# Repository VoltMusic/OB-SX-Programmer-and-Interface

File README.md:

# OB-SX-Programmer-and-Interface
This contains the Arduino code and KiCAD project file for creating a OB-SX Programmer and Interface.

The Interface plugs into the D-sub connector at the back of the OB-SX. It accesses the OB-XA's RAM and overwrites data linked to the voice board parameters.
The Programmer allows the user to program each parameter of the voices by sending messages to the Interface over a IC2 bus.

The RAM layout file shows how the parameters, key and gate signals are stored in RAM memory (can't promise this is %100 correct). Thank you to Prehistoricman for helping reverse-engineer the ROM of the OB-SX to find these relevant address locations.

I may re-visit this project again but design the board around the more powerfull teensy microcontroller. I had many issues with the slowness and memory leakage of the arduino.

Problems:
- And extra diode is required on the programmer board, I will update the PCB with this correction soon
- As you can see in the interface code the MIDI part is commented out, this is because it has many issues currently.

To-do:
- Upload example SD card patch files

Disclaimer:
- By using the code and PCB design files included in this repository, you take responsibility of any damage that may occur to your OB-SX. I highly recommend using these materials as a starting point for you to add and improve upon, if you do not have a good understanding of electronics and (Arduino) programming I do not recommend this project. These designs are open-source and therefore can be used as you wish.

Thank you

- Nile (Volter, VoltMusic)

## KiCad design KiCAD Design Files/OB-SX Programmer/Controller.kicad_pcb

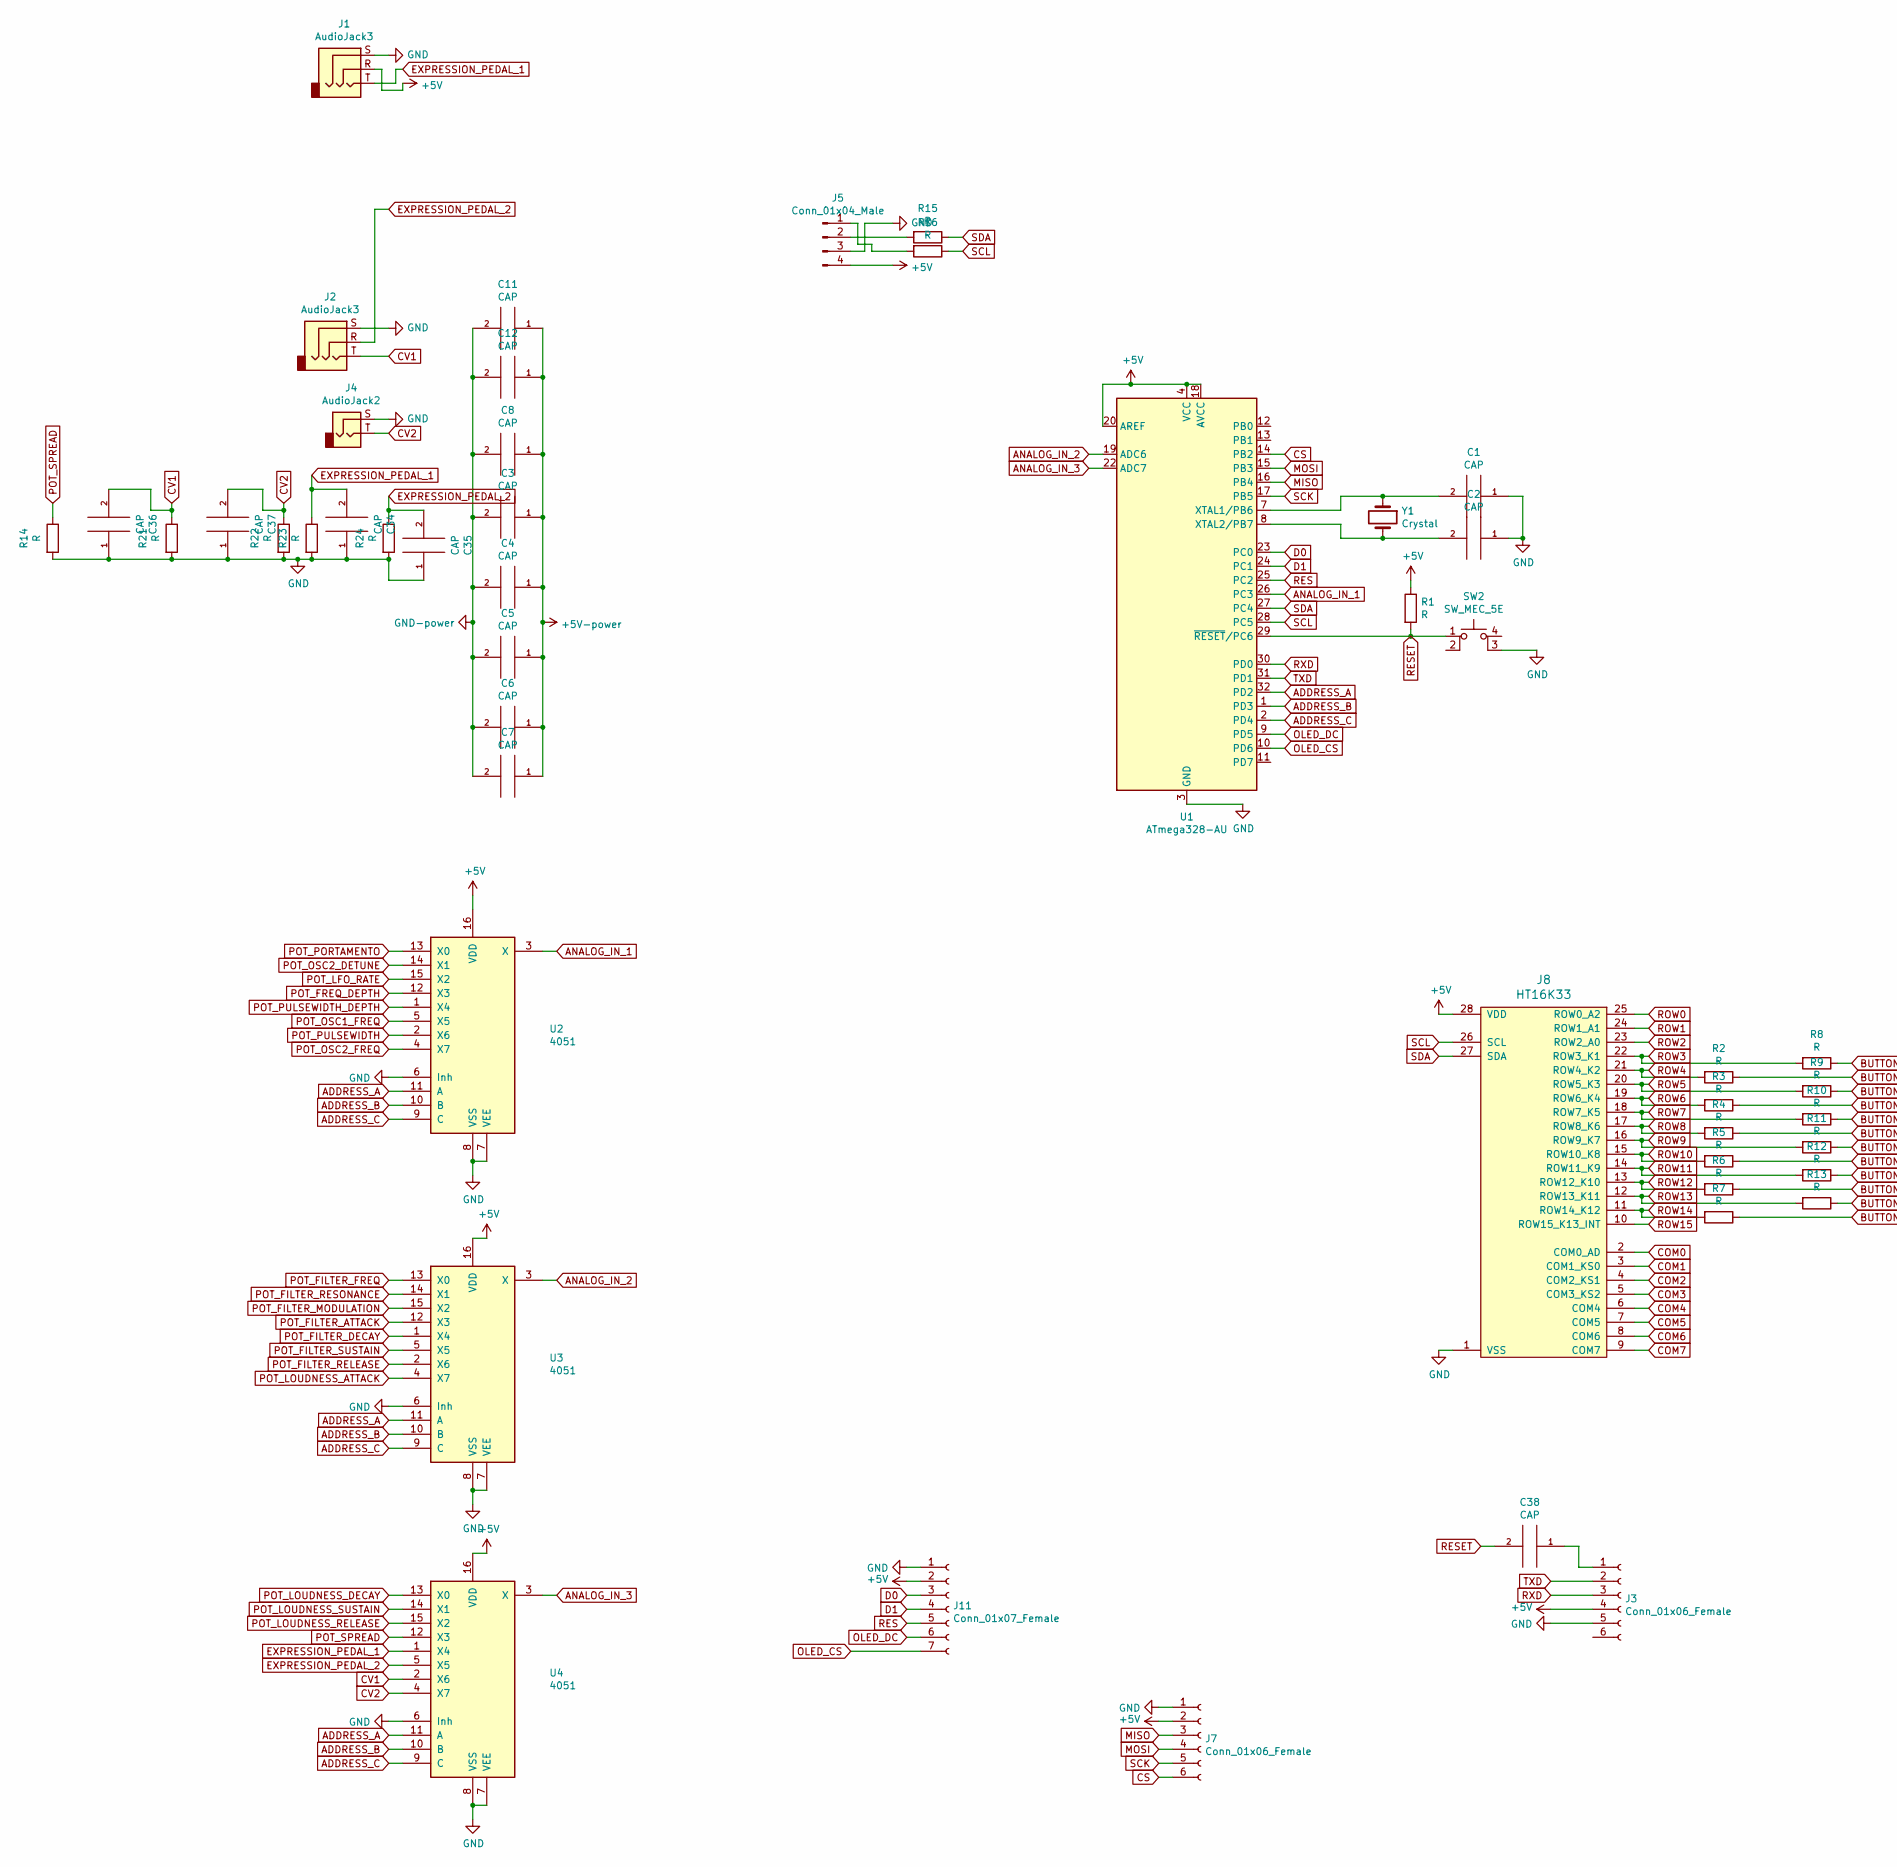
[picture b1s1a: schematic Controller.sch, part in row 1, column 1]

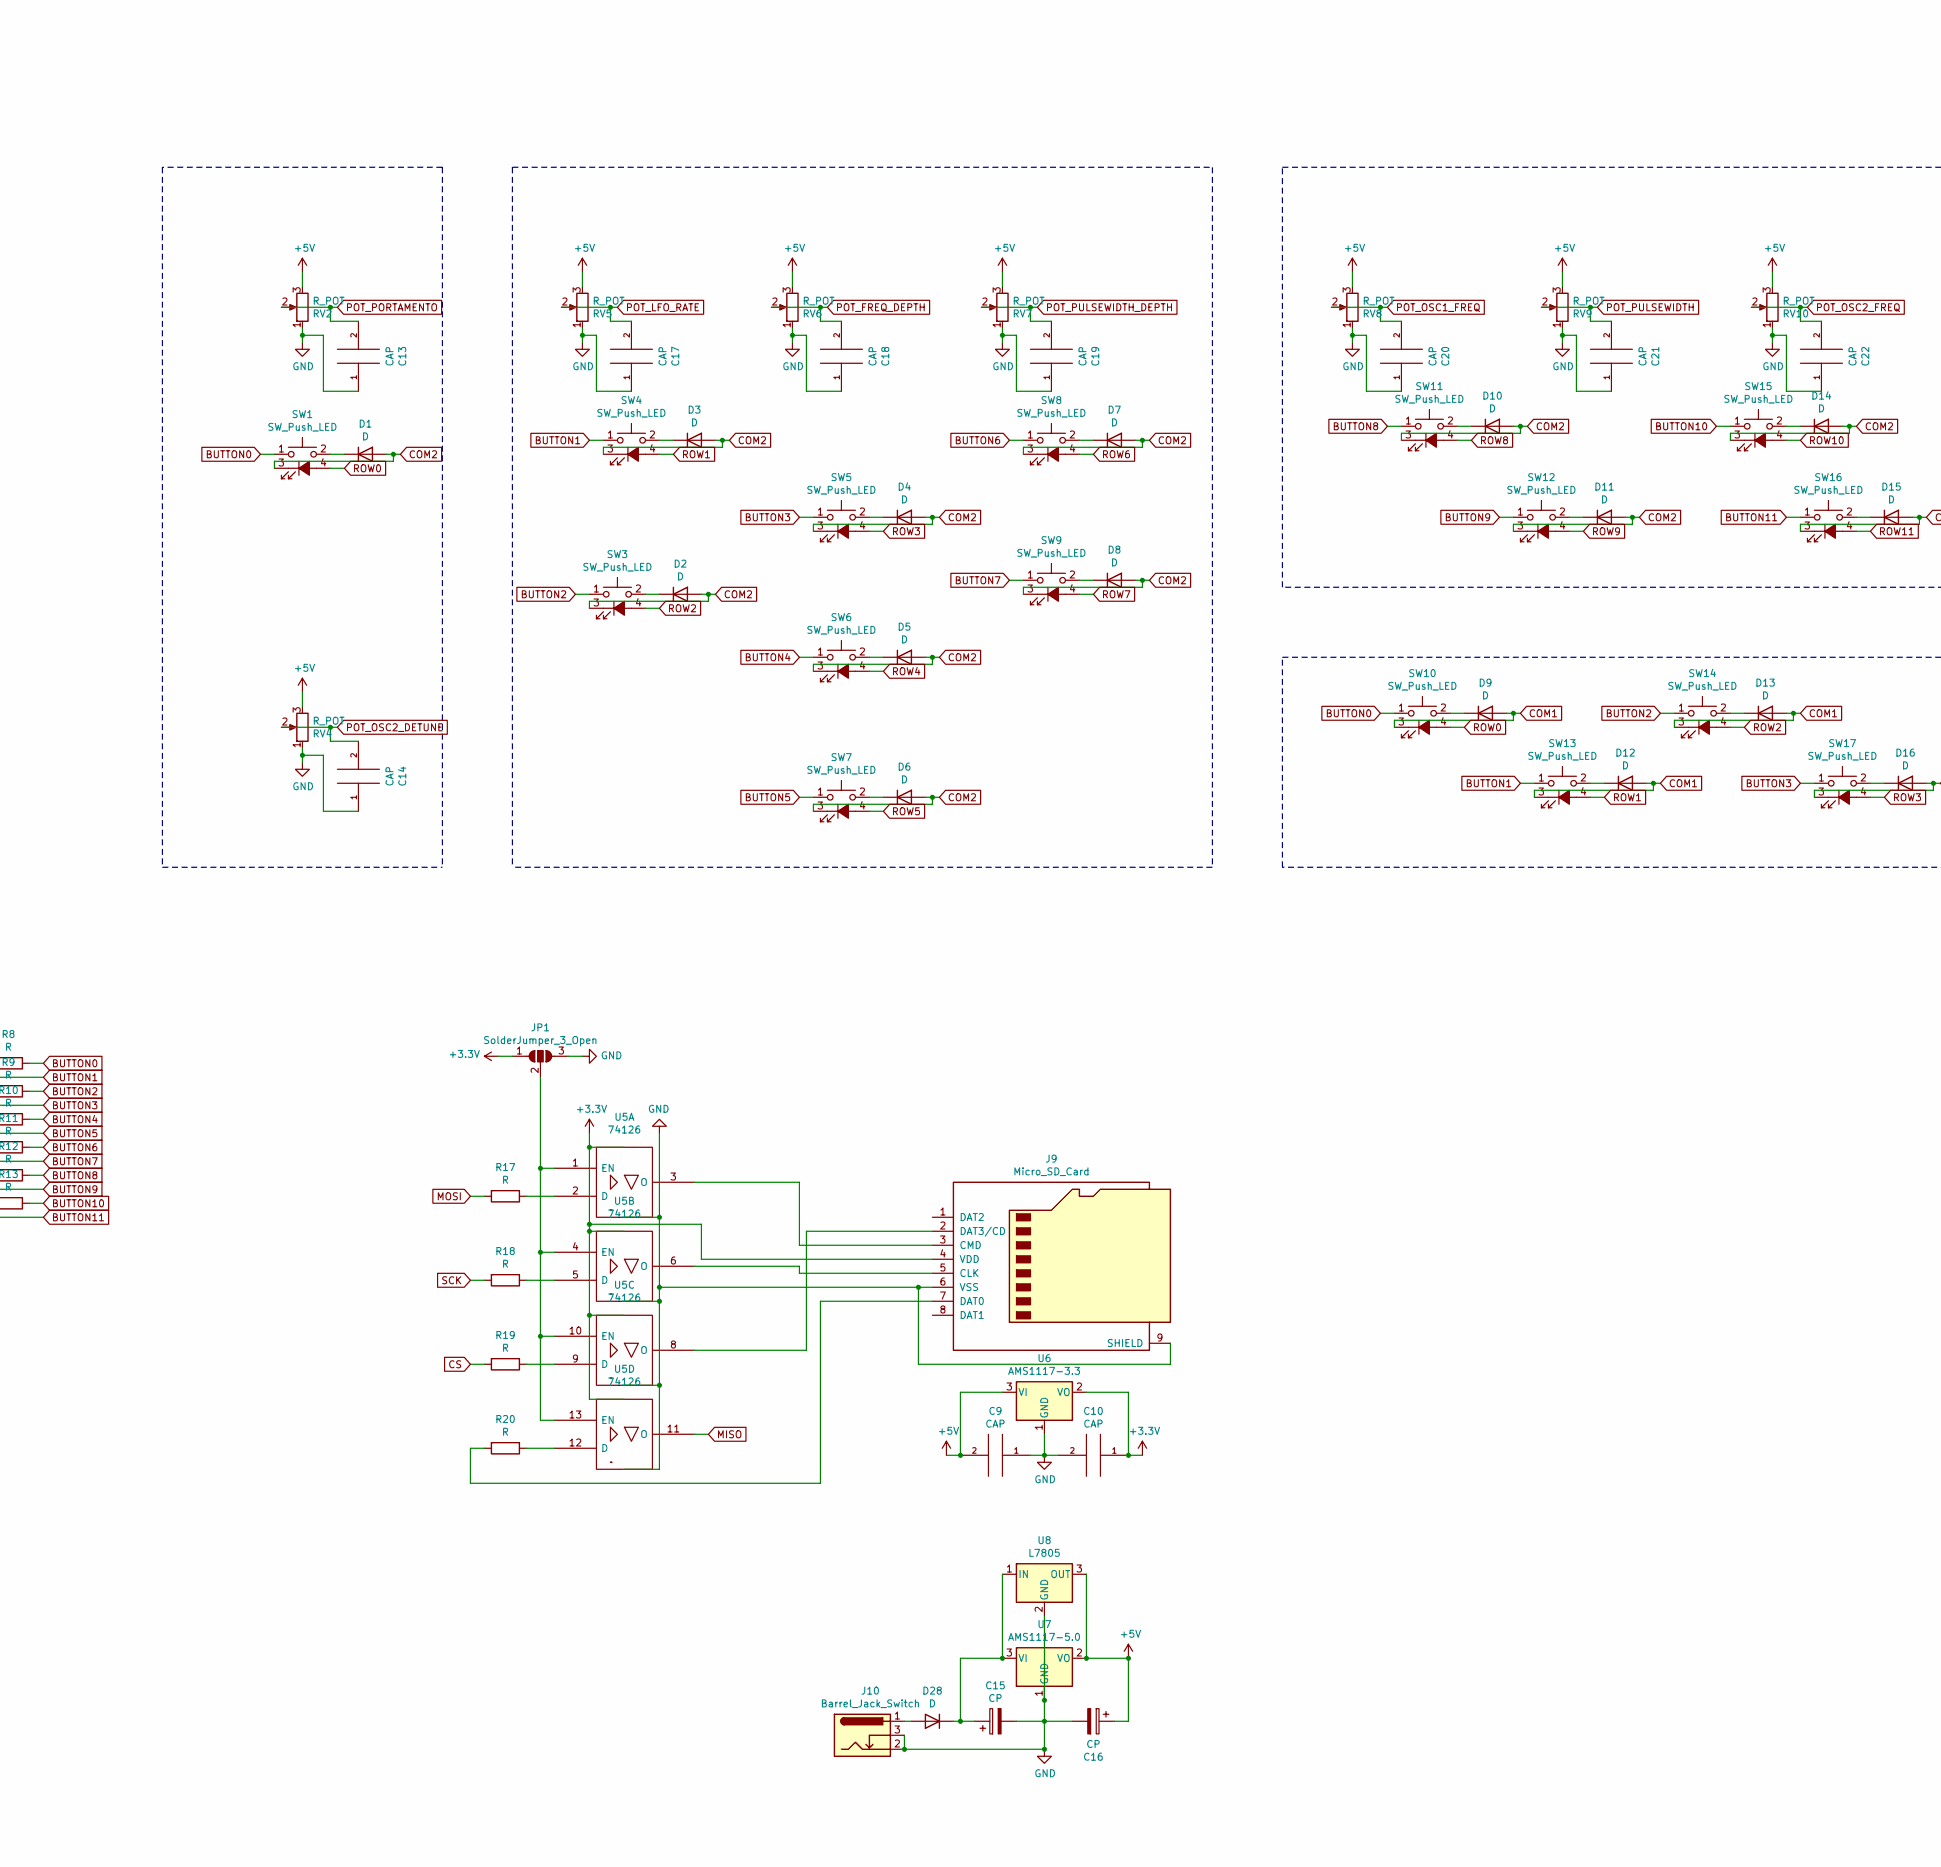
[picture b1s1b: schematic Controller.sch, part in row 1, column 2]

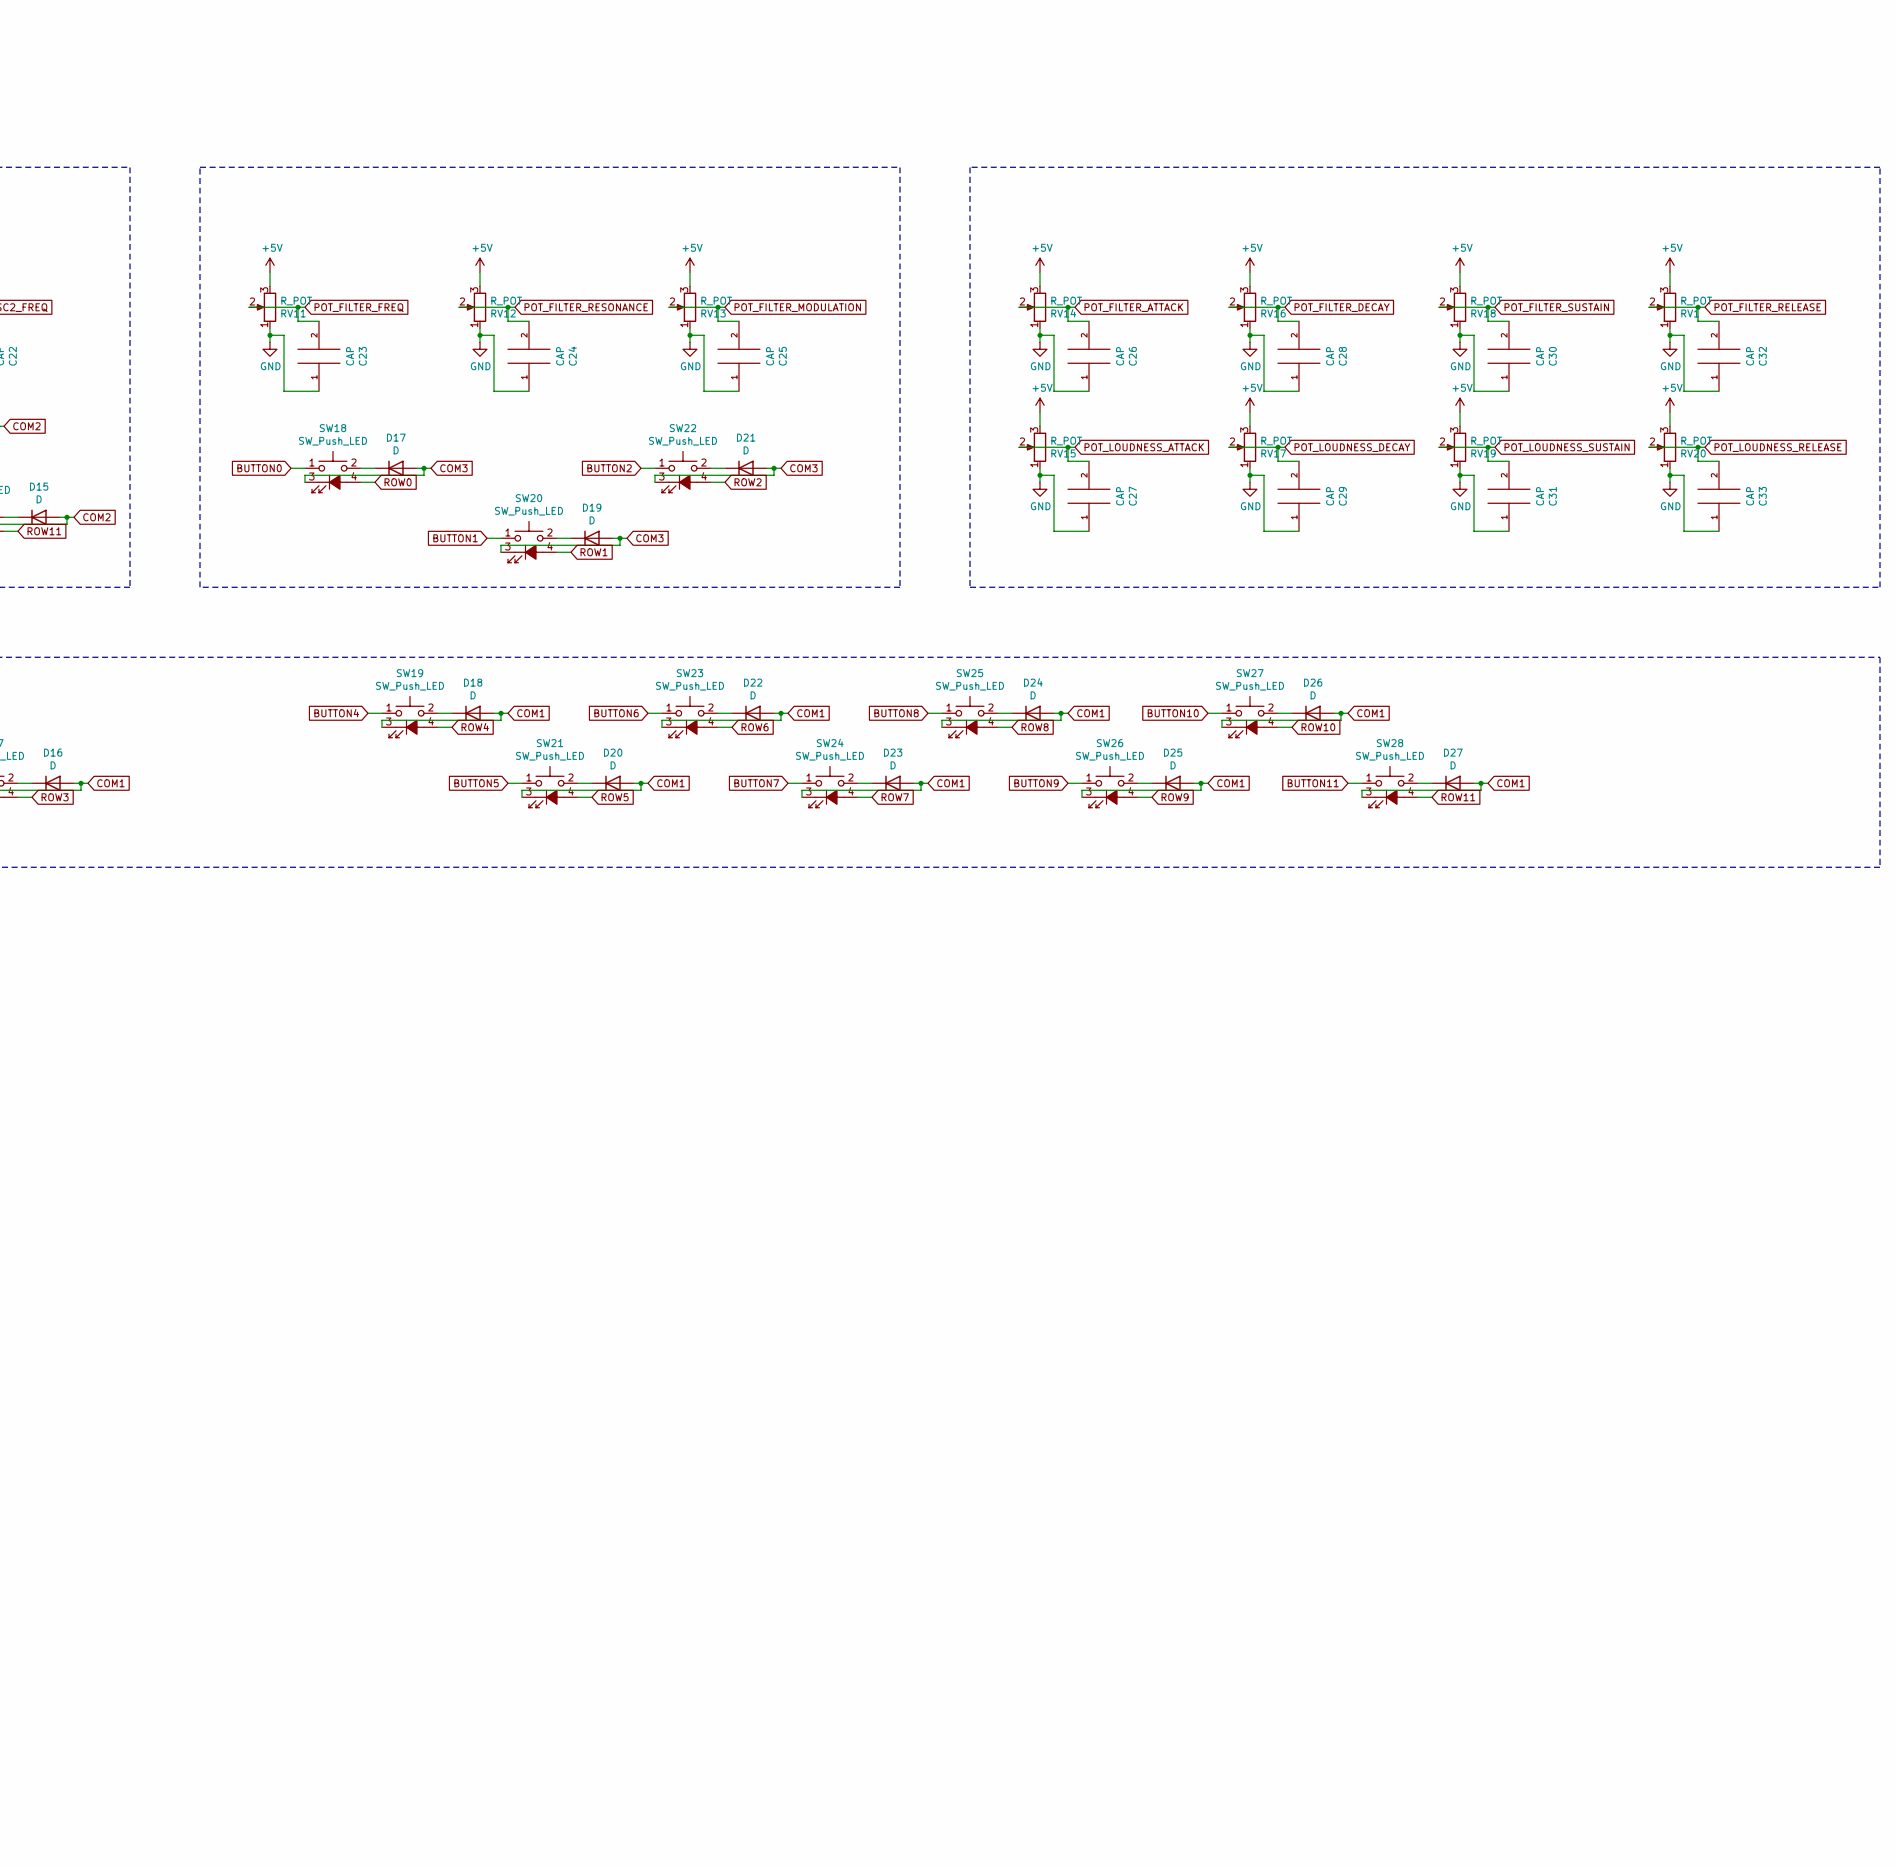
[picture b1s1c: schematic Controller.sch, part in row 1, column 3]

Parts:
C1, C2, C3, C4, C5, C6, C7, C8, C9, C10, C11, C12, C13, C14, C17, C18, C19, C20, C21, C22, C23, C24, C25, C26, C27, C28, C29, C30, C31, C32, C33, C34, C35, C36, C37, C38: CAP; C_0805_2012Metric_Pad1.18x1.45mm_HandSolder
C15, C16: CP; CP_Radial_D5.0mm_P2.00mm
D1, D2, D3, D4, D5, D6, D7, D8, D9, D10, D11, D12, D13, D14, D15, D16, D17, D18, D19, D20, D21, D22, D23, D24, D25, D26, D27: D; D_SOD-123
D28: D; D_DO-35_SOD27_P7.62mm_Horizontal
J1, J2: AudioJack3; Audio_Jack_3_Pin
J3, J7: Conn_01x06_Female; PinHeader_1x06_P2.54mm_Vertical
J4: AudioJack2; Audio_Jack_3_Pin
J5: Conn_01x04_Male; PJ320D_3.5mm_Jack
J8: HT16K33; SOIC-28W_7.5x17.9mm_P1.27mm
J9: Micro_SD_Card; Conn_uSDcard
J10: Barrel_Jack_Switch; CUI_PJ-002A
J11: Conn_01x07_Female; 1.3Inch_OLED_SPI
JP1: SolderJumper_3_Open; SolderJumper-3_P1.3mm_Open_RoundedPad1.0x1.5mm
R1, R2, R3, R4, R5, R6, R7, R8, R9, R10, R11, R12, R13, R14, R15, R16, R17, R18, R19, R20, R21, R22, R23, R24: R; R_0805_2012Metric_Pad1.20x1.40mm_HandSolder
RV1, RV2, RV4, RV5, RV6, RV7, RV8, RV9, RV10, RV11, RV12, RV13, RV14, RV15, RV16, RV17, RV18, RV19, RV20: R_POT; Potentiometer_Alpha_RD901F-40-00D_Single_Vertical
SW1, SW3, SW4, SW5, SW6, SW7, SW8, SW9, SW10, SW11, SW12, SW13, SW14, SW15, SW16, SW17, SW18, SW19, SW20, SW21, SW22, SW23, SW24, SW25, SW26, SW27, SW28: SW_Push_LED; Synth_Button
SW2: SW_MEC_5E; SW_TH_Tactile_Omron_B3F-10xx
U1: ATmega328-AU; TQFP-32_7x7mm_P0.8mm
U2, U3, U4: 4051; SO-16_3.9x9.9mm_P1.27mm
U5: 74126; SO-14_3.9x8.65mm_P1.27mm
U6: AMS1117-3.3; SOT-223-3_TabPin2
U7: AMS1117-5.0; SOT-223-3_TabPin2
U8: L7805; TO-220-3_Horizontal_TabDown
Y1: Crystal; Crystal_HC49-U_Vertical

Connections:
+3V3: C10.1, J9.4 (VDD), JP1.1 (A), U5.14 (VCC), U6.2 (VO)
ADDRESS_A: U1.32 (PD2), U2.11 (A), U3.11 (A), U4.11 (A)
ADDRESS_B: U1.1 (PD3), U2.10 (B), U3.10 (B), U4.10 (B)
ADDRESS_C: U1.2 (PD4), U2.9 (C), U3.9 (C), U4.9 (C)
ANALOG_IN_1: U1.26 (PC3), U2.3 (X)
ANALOG_IN_2: U1.19 (ADC6), U3.3 (X)
ANALOG_IN_3: U1.22 (ADC7), U4.3 (X)
BUTTON0: R8.1, SW1.1, SW10.1, SW18.1
BUTTON1: R2.1, SW4.1, SW13.1, SW20.1
BUTTON2: R9.1, SW3.1, SW14.1, SW22.1
BUTTON3: R3.1, SW5.1, SW17.1
BUTTON4: R10.1, SW6.1, SW19.1
BUTTON5: R4.1, SW7.1, SW21.1
BUTTON6: R11.1, SW8.1, SW23.1
BUTTON7: R5.1, SW9.1, SW24.1
BUTTON8: R12.1, SW11.1, SW25.1
BUTTON9: R6.1, SW12.1, SW26.1
BUTTON10: R13.1, SW15.1, SW27.1
BUTTON11: R7.1, SW16.1, SW28.1
COM0: J8.2 (COM0_AD)
COM1: D9.2 (A), D12.2 (A), D13.2 (A), D16.2 (A), D18.2 (A), D20.2 (A), D22.2 (A), D23.2 (A), D24.2 (A), D25.2 (A), D26.2 (A), D27.2 (A), J8.3 (COM1_KS0), SW10.3 (K), SW13.3 (K), SW14.3 (K), SW17.3 (K), SW19.3 (K), SW21.3 (K), SW23.3 (K), SW24.3 (K), SW25.3 (K), SW26.3 (K), SW27.3 (K), SW28.3 (K)
COM2: D1.2 (A), D2.2 (A), D3.2 (A), D4.2 (A), D5.2 (A), D6.2 (A), D7.2 (A), D8.2 (A), D10.2 (A), D11.2 (A), D14.2 (A), D15.2 (A), J8.4 (COM2_KS1), SW1.3 (K), SW3.3 (K), SW4.3 (K), SW5.3 (K), SW6.3 (K), SW7.3 (K), SW8.3 (K), SW9.3 (K), SW11.3 (K), SW12.3 (K), SW15.3 (K), SW16.3 (K)
COM3: D17.2 (A), D19.2 (A), D21.2 (A), J8.5 (COM3_KS2), SW18.3 (K), SW20.3 (K), SW22.3 (K)
COM4: J8.6 (COM4)
COM5: J8.7 (COM5)
COM6: J8.8 (COM6)
COM7: J8.9 (COM7)
CS: J7.6, R19.2, U1.14 (PB2)
CV1: C36.2, J2.T, R21.1, U4.2 (X6)
CV2: C37.2, J4.T, R22.1, U4.4 (X7)
D0: J11.3, U1.23 (PC0)
D1: J11.4, U1.24 (PC1)
EXPRESSION_PEDAL_1: C34.2, J1.T, R23.1, U4.1 (X4)
EXPRESSION_PEDAL_2: C35.2, J2.R, R24.1, U4.5 (X5)
MISO: J7.3, U1.16 (PB4), U5.11 (O)
MOSI: J7.4, R17.2, U1.15 (PB3)
unnamed: C1.2, U1.7 (XTAL1/PB6), Y1.1
unnamed: C2.2, U1.8 (XTAL2/PB7), Y1.2
unnamed: C15.1, D28.1 (K), U7.3 (VI), U8.1 (IN)
unnamed: C38.1, J3.1
unnamed: D1.1 (K), SW1.2
unnamed: D2.1 (K), SW3.2
unnamed: D3.1 (K), SW4.2
unnamed: D4.1 (K), SW5.2
unnamed: D5.1 (K), SW6.2
unnamed: D6.1 (K), SW7.2
unnamed: D7.1 (K), SW8.2
unnamed: D8.1 (K), SW9.2
unnamed: D9.1 (K), SW10.2
unnamed: D10.1 (K), SW11.2
unnamed: D11.1 (K), SW12.2
unnamed: D12.1 (K), SW13.2
unnamed: D13.1 (K), SW14.2
unnamed: D14.1 (K), SW15.2
unnamed: D15.1 (K), SW16.2
unnamed: D16.1 (K), SW17.2
unnamed: D17.1 (K), SW18.2
unnamed: D18.1 (K), SW19.2
unnamed: D19.1 (K), SW20.2
unnamed: D20.1 (K), SW21.2
unnamed: D21.1 (K), SW22.2
unnamed: D22.1 (K), SW23.2
unnamed: D23.1 (K), SW24.2
unnamed: D24.1 (K), SW25.2
unnamed: D25.1 (K), SW26.2
unnamed: D26.1 (K), SW27.2
unnamed: D27.1 (K), SW28.2
unnamed: D28.2 (A), J10.1
unnamed: J5.1, R16.2
unnamed: J5.2, R15.2
unnamed: J9.2 (DAT3/CD), U5.8 (O)
unnamed: J9.3 (CMD), U5.3 (O)
unnamed: J9.5 (CLK), U5.6 (O)
unnamed: J9.7 (DAT0), R20.2
unnamed: JP1.2 (C), U5.1 (EN), U5.4 (EN), U5.10 (EN), U5.13 (EN)
unnamed: R17.1, U5.2 (D)
unnamed: R18.1, U5.5 (D)
unnamed: R19.1, U5.9 (D)
unnamed: R20.1, U5.12 (D)
OLED_CS: J11.7, U1.10 (PD6)
OLED_DC: J11.6, U1.9 (PD5)
POT_FILTER_ATTACK: C26.2, RV14.2, U3.12 (X3)
POT_FILTER_DECAY: C28.2, RV16.2, U3.1 (X4)
POT_FILTER_FREQ: C23.2, RV11.2, U3.13 (X0)
POT_FILTER_MODULATION: C25.2, RV13.2, U3.15 (X2)
POT_FILTER_RELEASE: C32.2, RV1.2, U3.2 (X6)
POT_FILTER_RESONANCE: C24.2, RV12.2, U3.14 (X1)
POT_FILTER_SUSTAIN: C30.2, RV18.2, U3.5 (X5)
POT_FREQ_DEPTH: C18.2, RV6.2, U2.12 (X3)
POT_LFO_RATE: C17.2, RV5.2, U2.15 (X2)
POT_LOUDNESS_ATTACK: C27.2, RV15.2, U3.4 (X7)
POT_LOUDNESS_DECAY: C29.2, RV17.2, U4.13 (X0)
POT_LOUDNESS_RELEASE: C33.2, RV20.2, U4.15 (X2)
POT_LOUDNESS_SUSTAIN: C31.2, RV19.2, U4.14 (X1)
POT_OSC1_FREQ: C20.2, RV8.2, U2.5 (X5)
POT_OSC2_DETUNE: C14.2, RV4.2, U2.14 (X1)
POT_OSC2_FREQ: C22.2, RV10.2, U2.4 (X7)
POT_PORTAMENTO: C13.2, RV2.2, U2.13 (X0)
POT_PULSEWIDTH: C21.2, RV9.2, U2.2 (X6)
POT_PULSEWIDTH_DEPTH: C19.2, RV7.2, U2.1 (X4)
POT_SPREAD: R14.1, U4.12 (X3)
RES: J11.5, U1.25 (PC2)
RESET: C38.2, R1.2, SW2.1, U1.29 (~RESET~/PC6)
ROW0: J8.25 (ROW0_A2), SW1.4 (A), SW10.4 (A), SW18.4 (A)
ROW1: J8.24 (ROW1_A1), SW4.4 (A), SW13.4 (A), SW20.4 (A)
ROW2: J8.23 (ROW2_A0), SW3.4 (A), SW14.4 (A), SW22.4 (A)
ROW3: J8.22 (ROW3_K1), R8.2, SW5.4 (A), SW17.4 (A)
ROW4: J8.21 (ROW4_K2), R2.2, SW6.4 (A), SW19.4 (A)
ROW5: J8.20 (ROW5_K3), R9.2, SW7.4 (A), SW21.4 (A)
ROW6: J8.19 (ROW6_K4), R3.2, SW8.4 (A), SW23.4 (A)
ROW7: J8.18 (ROW7_K5), R10.2, SW9.4 (A), SW24.4 (A)
ROW8: J8.17 (ROW8_K6), R4.2, SW11.4 (A), SW25.4 (A)
ROW9: J8.16 (ROW9_K7), R11.2, SW12.4 (A), SW26.4 (A)
ROW10: J8.15 (ROW10_K8), R5.2, SW15.4 (A), SW27.4 (A)
ROW11: J8.14 (ROW11_K9), R12.2, SW16.4 (A), SW28.4 (A)
ROW12: J8.13 (ROW12_K10), R6.2
ROW13: J8.12 (ROW13_K11), R13.2
ROW14: J8.11 (ROW14_K12), R7.2
ROW15: J8.10 (ROW15_K13_INT)
RXD: J3.3, U1.30 (PD0)
SCK: J7.5, R18.2, U1.17 (PB5)
SCL: J8.26 (SCL), R16.1, U1.28 (PC5)
SDA: J8.27 (SDA), R15.1, U1.27 (PC4)
TXD: J3.2, U1.31 (PD1)

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
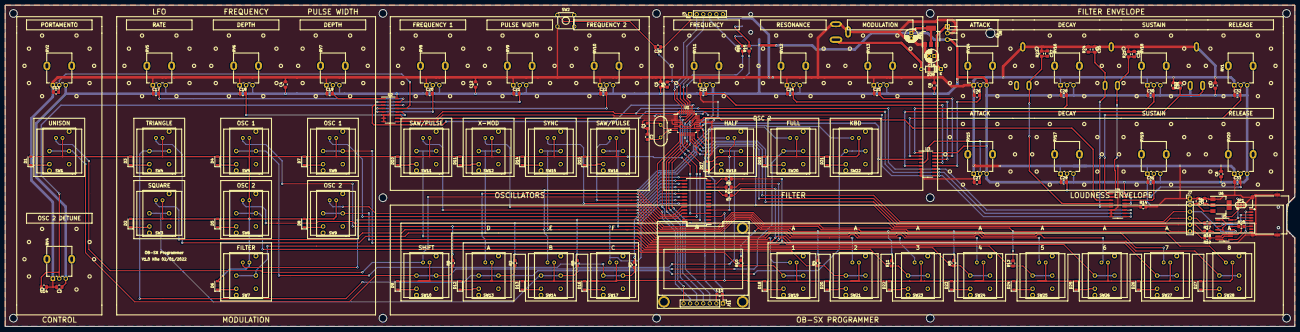
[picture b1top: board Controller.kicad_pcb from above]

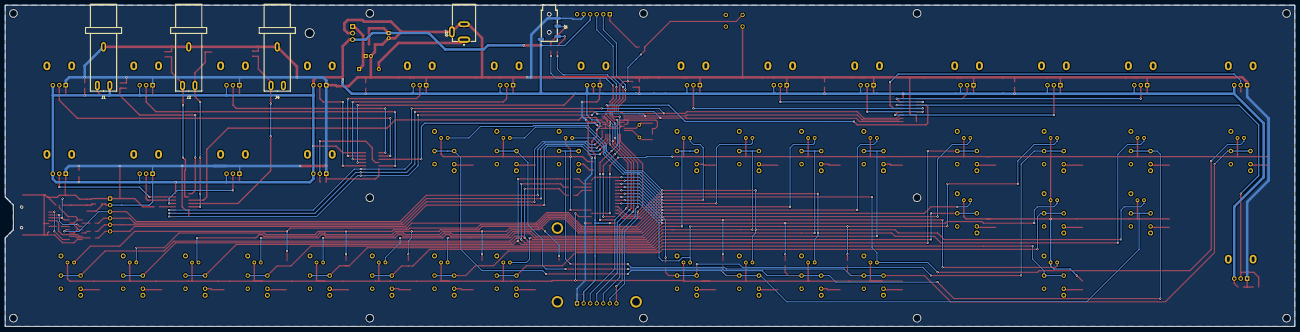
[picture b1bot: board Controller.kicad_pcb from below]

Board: 2 copper layers, 499.7 x 124.5 mm, 157 parts (5 on the bottom side), 120 nets.

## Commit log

2022-01-02 Create KiCAD Design Files
